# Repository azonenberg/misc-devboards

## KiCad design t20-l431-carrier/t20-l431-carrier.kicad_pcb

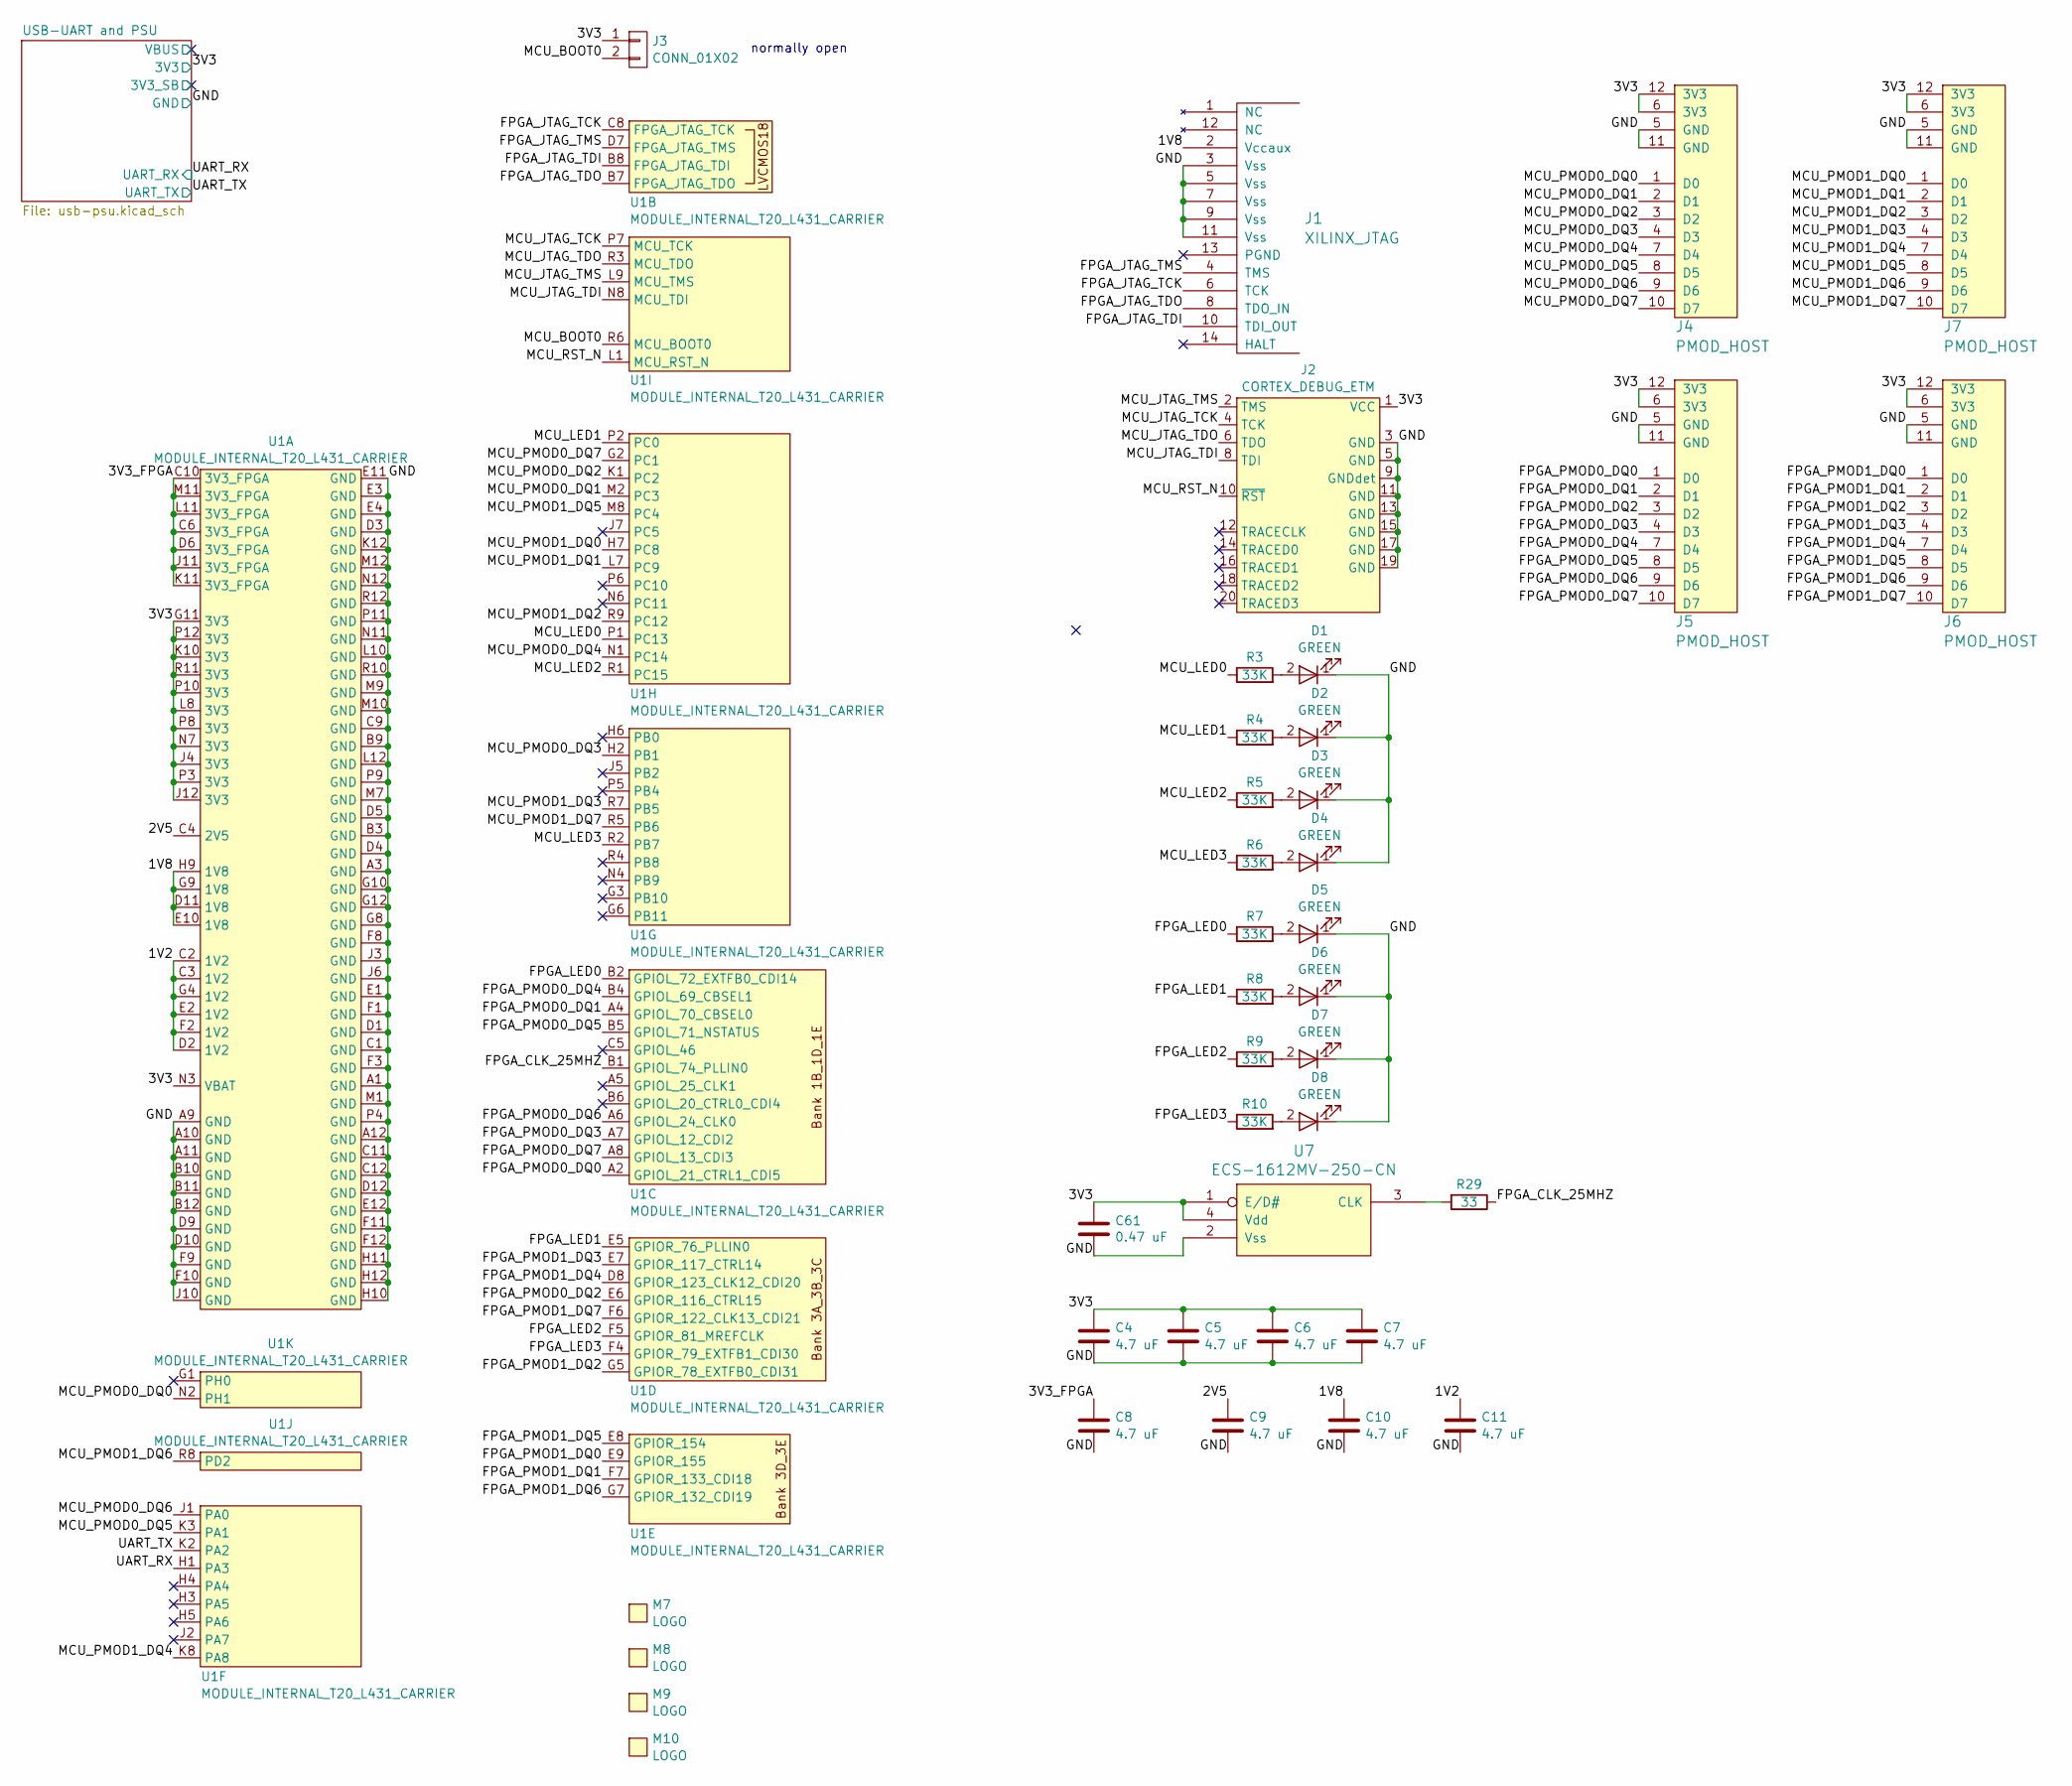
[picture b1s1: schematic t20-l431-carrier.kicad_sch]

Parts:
C4, C5, C6, C7, C8, C9, C10, C11: 4.7 uF; EIA_0603_CAP_NOSILK
C61: 0.47 uF; EIA_0402_CAP_NOSILK
D1, D2, D3, D4, D5, D6, D7, D8: GREEN; EIA_0402_LED
J1: XILINX_JTAG; XILINX_JTAG_PTH_MOLEX_0878311420
J2: CORTEX_DEBUG_ETM; CONN_HEADER_1.27MM_2x10_SMT_SAMTEC_FTSH-110-01-L-DV-K
J3: CONN_01X02; CONN_HEADER_2.54MM_1x2
J4, J5, J6, J7: PMOD_HOST; CONN_HEADER_2.54MM_2x6_RA_PMOD_HOST
M7: LOGO; LONGTHING-1200DPI
M8: LOGO; Logo_silk_ROHS_5x2.8mm
M9: LOGO; Logo_silk_WEEE_3.4x5mm
M10: LOGO; Logo_silk_OSHW_6x6mm
R3, R4, R5, R6, R7, R8, R9, R10: 33K; EIA_0402_RES_NOSILK
R29: 33; EIA_0402_RES_NOSILK
U1: MODULE_INTERNAL_T20_L431_CARRIER
U7: ECS-1612MV-250-CN; OSCILLATOR_1.6x1.2

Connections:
/1V2: C11.1, U1.C2 (1V2), U1.C3 (1V2), U1.D2 (1V2), U1.E2 (1V2), U1.F2 (1V2), U1.G4 (1V2)
/1V8: C10.1, J1.2 (Vccaux), U1.D11 (1V8), U1.E10 (1V8), U1.G9 (1V8), U1.H9 (1V8)
/2V5: C9.1, U1.C4 (2V5)
/3V3: C4.1, C5.1, C6.1, C7.1, C61.1, J2.1 (VCC), J3.1, J4.6 (3V3), J4.12 (3V3), J5.6 (3V3), J5.12 (3V3), J6.6 (3V3), J6.12 (3V3), J7.6 (3V3), J7.12 (3V3), U1.G11 (3V3), U1.J4 (3V3), U1.J12 (3V3), U1.K10 (3V3), U1.L8 (3V3), U1.N3 (VBAT), U1.N7 (3V3), U1.P3 (3V3), U1.P8 (3V3), U1.P10 (3V3), U1.P12 (3V3), U1.R11 (3V3), U7.1 (E/D#), U7.4 (Vdd); also elsewhere on the board
/3V3_FPGA: C8.1, U1.C6 (3V3_FPGA), U1.C10 (3V3_FPGA), U1.D6 (3V3_FPGA), U1.J11 (3V3_FPGA), U1.K11 (3V3_FPGA), U1.L11 (3V3_FPGA), U1.M11 (3V3_FPGA)
/FPGA_CLK_25MHZ: R29.1, U1.B1 (GPIOL_74_PLLIN0)
/FPGA_JTAG_TCK: J1.6 (TCK), U1.C8 (FPGA_JTAG_TCK)
/FPGA_JTAG_TDI: J1.10 (TDI_OUT), U1.B8 (FPGA_JTAG_TDI)
/FPGA_JTAG_TDO: J1.8 (TDO_IN), U1.B7 (FPGA_JTAG_TDO)
/FPGA_JTAG_TMS: J1.4 (TMS), U1.D7 (FPGA_JTAG_TMS)
/FPGA_LED0: R7.1, U1.B2 (GPIOL_72_EXTFB0_CDI14)
/FPGA_LED1: R8.1, U1.E5 (GPIOR_76_PLLIN0)
/FPGA_LED2: R9.1, U1.F5 (GPIOR_81_MREFCLK)
/FPGA_LED3: R10.1, U1.F4 (GPIOR_79_EXTFB1_CDI30)
/FPGA_PMOD0_DQ0: J5.1 (D0), U1.A2 (GPIOL_21_CTRL1_CDI5)
/FPGA_PMOD0_DQ1: J5.2 (D1), U1.A4 (GPIOL_70_CBSEL0)
/FPGA_PMOD0_DQ2: J5.3 (D2), U1.E6 (GPIOR_116_CTRL15)
/FPGA_PMOD0_DQ3: J5.4 (D3), U1.A7 (GPIOL_12_CDI2)
/FPGA_PMOD0_DQ4: J5.7 (D4), U1.B4 (GPIOL_69_CBSEL1)
/FPGA_PMOD0_DQ5: J5.8 (D5), U1.B5 (GPIOL_71_NSTATUS)
/FPGA_PMOD0_DQ6: J5.9 (D6), U1.A6 (GPIOL_24_CLK0)
/FPGA_PMOD0_DQ7: J5.10 (D7), U1.A8 (GPIOL_13_CDI3)
/FPGA_PMOD1_DQ0: J6.1 (D0), U1.E9 (GPIOR_155)
/FPGA_PMOD1_DQ1: J6.2 (D1), U1.F7 (GPIOR_133_CDI18)
/FPGA_PMOD1_DQ2: J6.3 (D2), U1.G5 (GPIOR_78_EXTFB0_CDI31)
/FPGA_PMOD1_DQ3: J6.4 (D3), U1.E7 (GPIOR_117_CTRL14)
/FPGA_PMOD1_DQ4: J6.7 (D4), U1.D8 (GPIOR_123_CLK12_CDI20)
/FPGA_PMOD1_DQ5: J6.8 (D5), U1.E8 (GPIOR_154)
/FPGA_PMOD1_DQ6: J6.9 (D6), U1.G7 (GPIOR_132_CDI19)
/FPGA_PMOD1_DQ7: J6.10 (D7), U1.F6 (GPIOR_122_CLK13_CDI21)
/GND: C4.2, C5.2, C6.2, C7.2, C8.2, C9.2, C10.2, C11.2, C61.2, D1.1 (K), D2.1 (K), D3.1 (K), D4.1 (K), D5.1 (K), D6.1 (K), D7.1 (K), D8.1 (K), J1.3 (Vss), J1.5 (Vss), J1.7 (Vss), J1.9 (Vss), J1.11 (Vss), J2.3 (GND), J2.5 (GND), J2.9 (GNDdet), J2.11 (GND), J2.13 (GND), J2.15 (GND), J2.17 (GND), J2.19 (GND), J4.5 (GND), J4.11 (GND), J5.5 (GND), J5.11 (GND), J6.5 (GND), J6.11 (GND), J7.5 (GND), J7.11 (GND), U1.A1 (GND), U1.A3 (GND), U1.A9 (GND), U1.A10 (GND), U1.A11 (GND), U1.A12 (GND), U1.B3 (GND), U1.B9 (GND), U1.B10 (GND), U1.B11 (GND), U1.B12 (GND), U1.C1 (GND), U1.C9 (GND), U1.C11 (GND), U1.C12 (GND), U1.D1 (GND), U1.D3 (GND), U1.D4 (GND), U1.D5 (GND), U1.D9 (GND), U1.D10 (GND), U1.D12 (GND), U1.E1 (GND), U1.E3 (GND), U1.E4 (GND), U1.E11 (GND), U1.E12 (GND), U1.F1 (GND), U1.F3 (GND), U1.F8 (GND), U1.F9 (GND), U1.F10 (GND), U1.F11 (GND), U1.F12 (GND), U1.G8 (GND), U1.G10 (GND), U1.G12 (GND), U1.H10 (GND), U1.H11 (GND), U1.H12 (GND), U1.J3 (GND), U1.J6 (GND), U1.J10 (GND), U1.K12 (GND), U1.L10 (GND), U1.L12 (GND), U1.M1 (GND), U1.M7 (GND), U1.M9 (GND), U1.M10 (GND), U1.M12 (GND), U1.N11 (GND), U1.N12 (GND), U1.P4 (GND), U1.P9 (GND), U1.P11 (GND), U1.R10 (GND), U1.R12 (GND), U7.2 (Vss); also elsewhere on the board
/MCU_BOOT0: J3.2, U1.R6 (MCU_BOOT0)
/MCU_JTAG_TCK: J2.4 (TCK), U1.P7 (MCU_TCK)
/MCU_JTAG_TDI: J2.8 (TDI), U1.N8 (MCU_TDI)
/MCU_JTAG_TDO: J2.6 (TDO), U1.R3 (MCU_TDO)
/MCU_JTAG_TMS: J2.2 (TMS), U1.L9 (MCU_TMS)
/MCU_LED0: R3.1, U1.P1 (PC13)
/MCU_LED1: R4.1, U1.P2 (PC0)
/MCU_LED2: R5.1, U1.R1 (PC15)
/MCU_LED3: R6.1, U1.R2 (PB7)
/MCU_PMOD0_DQ0: J4.1 (D0), U1.N2 (PH1)
/MCU_PMOD0_DQ1: J4.2 (D1), U1.M2 (PC3)
/MCU_PMOD0_DQ2: J4.3 (D2), U1.K1 (PC2)
/MCU_PMOD0_DQ3: J4.4 (D3), U1.H2 (PB1)
/MCU_PMOD0_DQ4: J4.7 (D4), U1.N1 (PC14)
/MCU_PMOD0_DQ5: J4.8 (D5), U1.K3 (PA1)
/MCU_PMOD0_DQ6: J4.9 (D6), U1.J1 (PA0)
/MCU_PMOD0_DQ7: J4.10 (D7), U1.G2 (PC1)
/MCU_PMOD1_DQ0: J7.1 (D0), U1.H7 (PC8)
/MCU_PMOD1_DQ1: J7.2 (D1), U1.L7 (PC9)
/MCU_PMOD1_DQ2: J7.3 (D2), U1.R9 (PC12)
/MCU_PMOD1_DQ3: J7.4 (D3), U1.R7 (PB5)
/MCU_PMOD1_DQ4: J7.7 (D4), U1.K8 (PA8)
/MCU_PMOD1_DQ5: J7.8 (D5), U1.M8 (PC4)
/MCU_PMOD1_DQ6: J7.9 (D6), U1.R8 (PD2)
/MCU_PMOD1_DQ7: J7.10 (D7), U1.R5 (PB6)
/MCU_RST_N: J2.10 (~RST), U1.L1 (MCU_RST_N)
/UART_RX: U1.H1 (PA3); also elsewhere on the board
/UART_TX: U1.K2 (PA2); also elsewhere on the board
unnamed: D1.2 (A), R3.2
unnamed: D2.2 (A), R4.2
unnamed: D3.2 (A), R5.2
unnamed: D4.2 (A), R6.2
unnamed: D5.2 (A), R7.2
unnamed: D6.2 (A), R8.2
unnamed: D7.2 (A), R9.2
unnamed: D8.2 (A), R10.2
unnamed: R29.2, U7.3 (CLK)

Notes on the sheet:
normally open

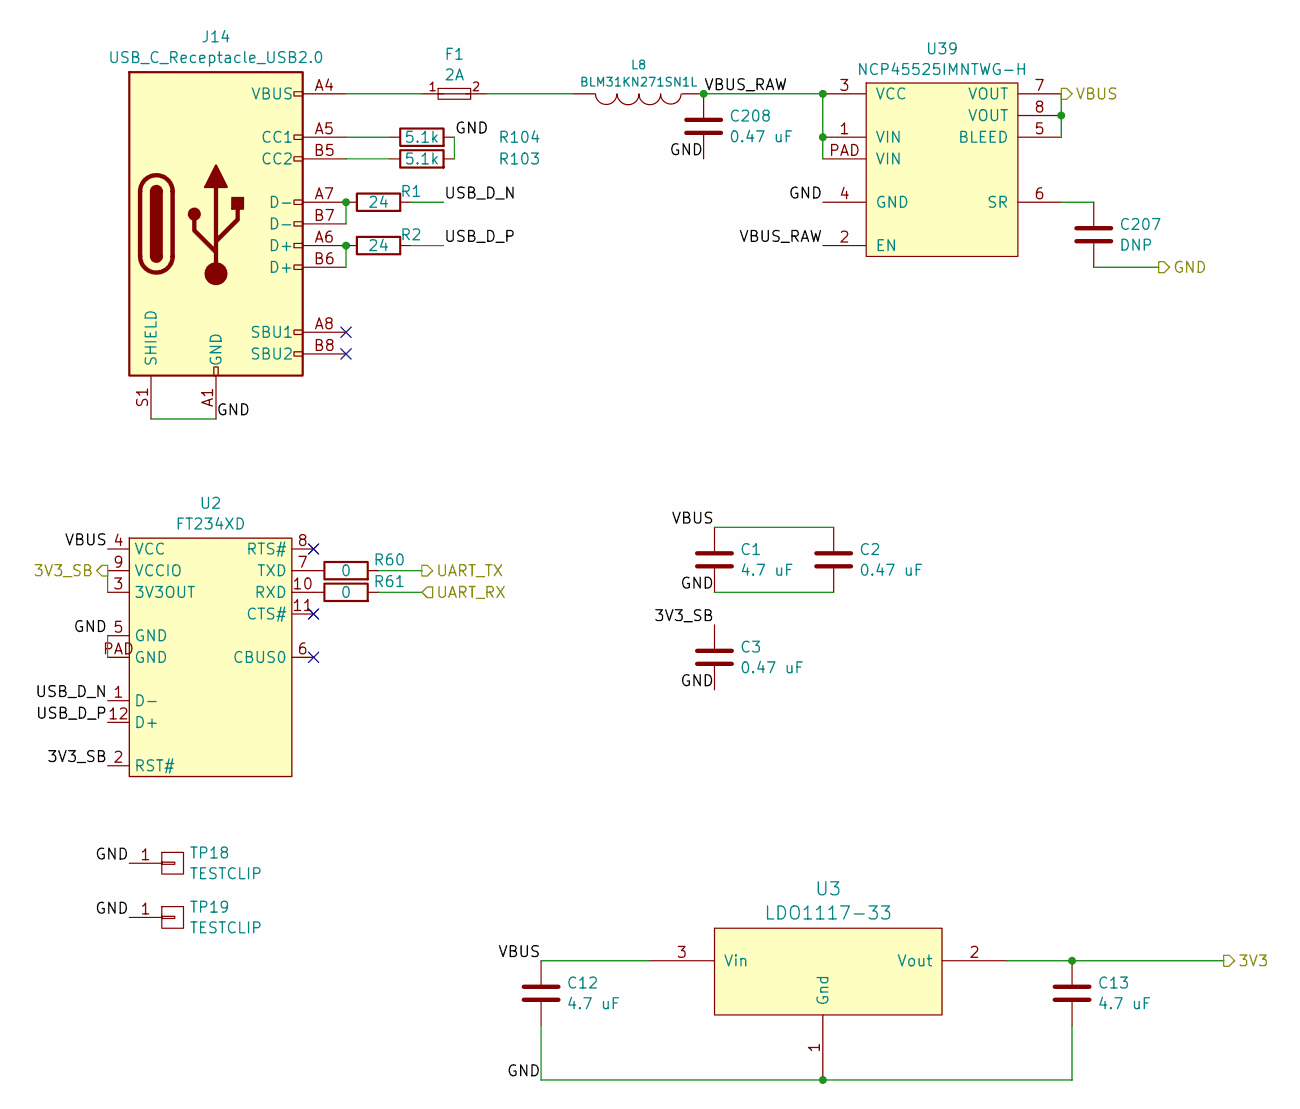
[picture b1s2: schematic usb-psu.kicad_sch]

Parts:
C1, C12, C13: 4.7 uF; EIA_0603_CAP_NOSILK
C2, C3, C208: 0.47 uF; EIA_0402_CAP_NOSILK
C207: DNP; EIA_0402_CAP_NOSILK
F1: 2A; EIA_0402_RES_NOSILK
J14: USB_C_Receptacle_USB2.0; GCT_USB4500-03-0-A-PIP
L8: BLM31KN271SN1L; EIA_1206_CAP_NOSILK
R1, R2: 24; EIA_0402_RES_NOSILK
R60, R61: 0; EIA_0402_RES_NOSILK
R103, R104: 5.1k; EIA_0402_RES_NOSILK
TP18, TP19: TESTCLIP; TESTPOINT_SMT_KEYSTONE_5016
U2: FT234XD; DFN_12_0.45MM_3x3MM
U3: LDO1117-33; SOT223-4
U39: NCP45525IMNTWG-H; DFN_8_0.5MM_2x2MM

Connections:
/3V3: C13.1, U3.2 (Vout); also elsewhere on the board
/GND: C1.2, C2.2, C3.2, C12.2, C13.2, C207.2, C208.2, J14.A1 (GND), J14.A12 (GND), J14.B1 (GND), J14.B12 (GND), J14.S1 (SHIELD), R103.2, R104.2, TP18.1, TP19.1, U2.5 (GND), U2.PAD (GND), U3.1 (Gnd), U39.4 (GND); also elsewhere on the board
/UART_RX: R61.2; also elsewhere on the board
/UART_TX: R60.2; also elsewhere on the board
/USB-UART and PSU/3V3_SB: C3.1, U2.2 (RST#), U2.3 (3V3OUT), U2.9 (VCCIO)
/USB-UART and PSU/USB_D_N: R1.2, U2.1 (D-)
/USB-UART and PSU/USB_D_P: R2.2, U2.12 (D+)
/USB-UART and PSU/VBUS: C1.1, C2.1, C12.1, U2.4 (VCC), U3.3 (Vin), U39.5 (BLEED), U39.7 (VOUT), U39.8 (VOUT)
/USB-UART and PSU/VBUS_RAW: C208.1, L8.1, U39.1 (VIN), U39.2 (EN), U39.3 (VCC), U39.PAD (VIN)
unnamed: F1.1, J14.A4 (VBUS), J14.A9 (VBUS), J14.B4 (VBUS), J14.B9 (VBUS)
unnamed: F1.2, L8.2
unnamed: J14.A5 (CC1), R104.1
unnamed: J14.B5 (CC2), R103.1
unnamed: J14.A6 (D+), J14.B6 (D+), R2.1
unnamed: J14.A7 (D-), J14.B7 (D-), R1.1
unnamed: R61.1, U2.10 (RXD)
unnamed: R60.1, U2.7 (TXD)
unnamed: C207.1, U39.6 (SR)

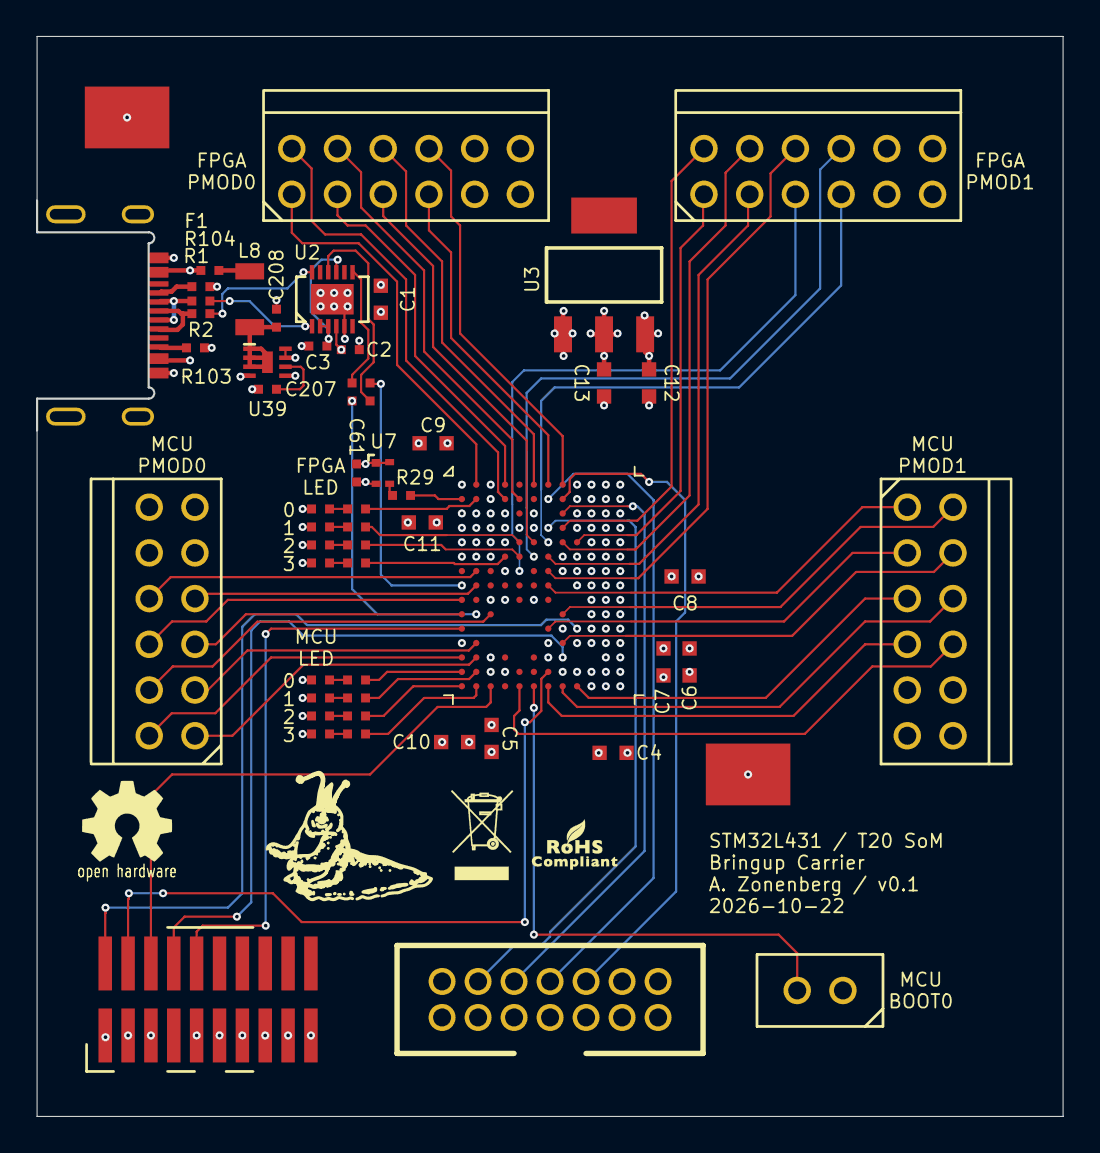
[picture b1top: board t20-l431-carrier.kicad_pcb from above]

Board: 4 copper layers, 57.0 x 60.0 mm, 60 parts (0 on the bottom side), 82 nets.

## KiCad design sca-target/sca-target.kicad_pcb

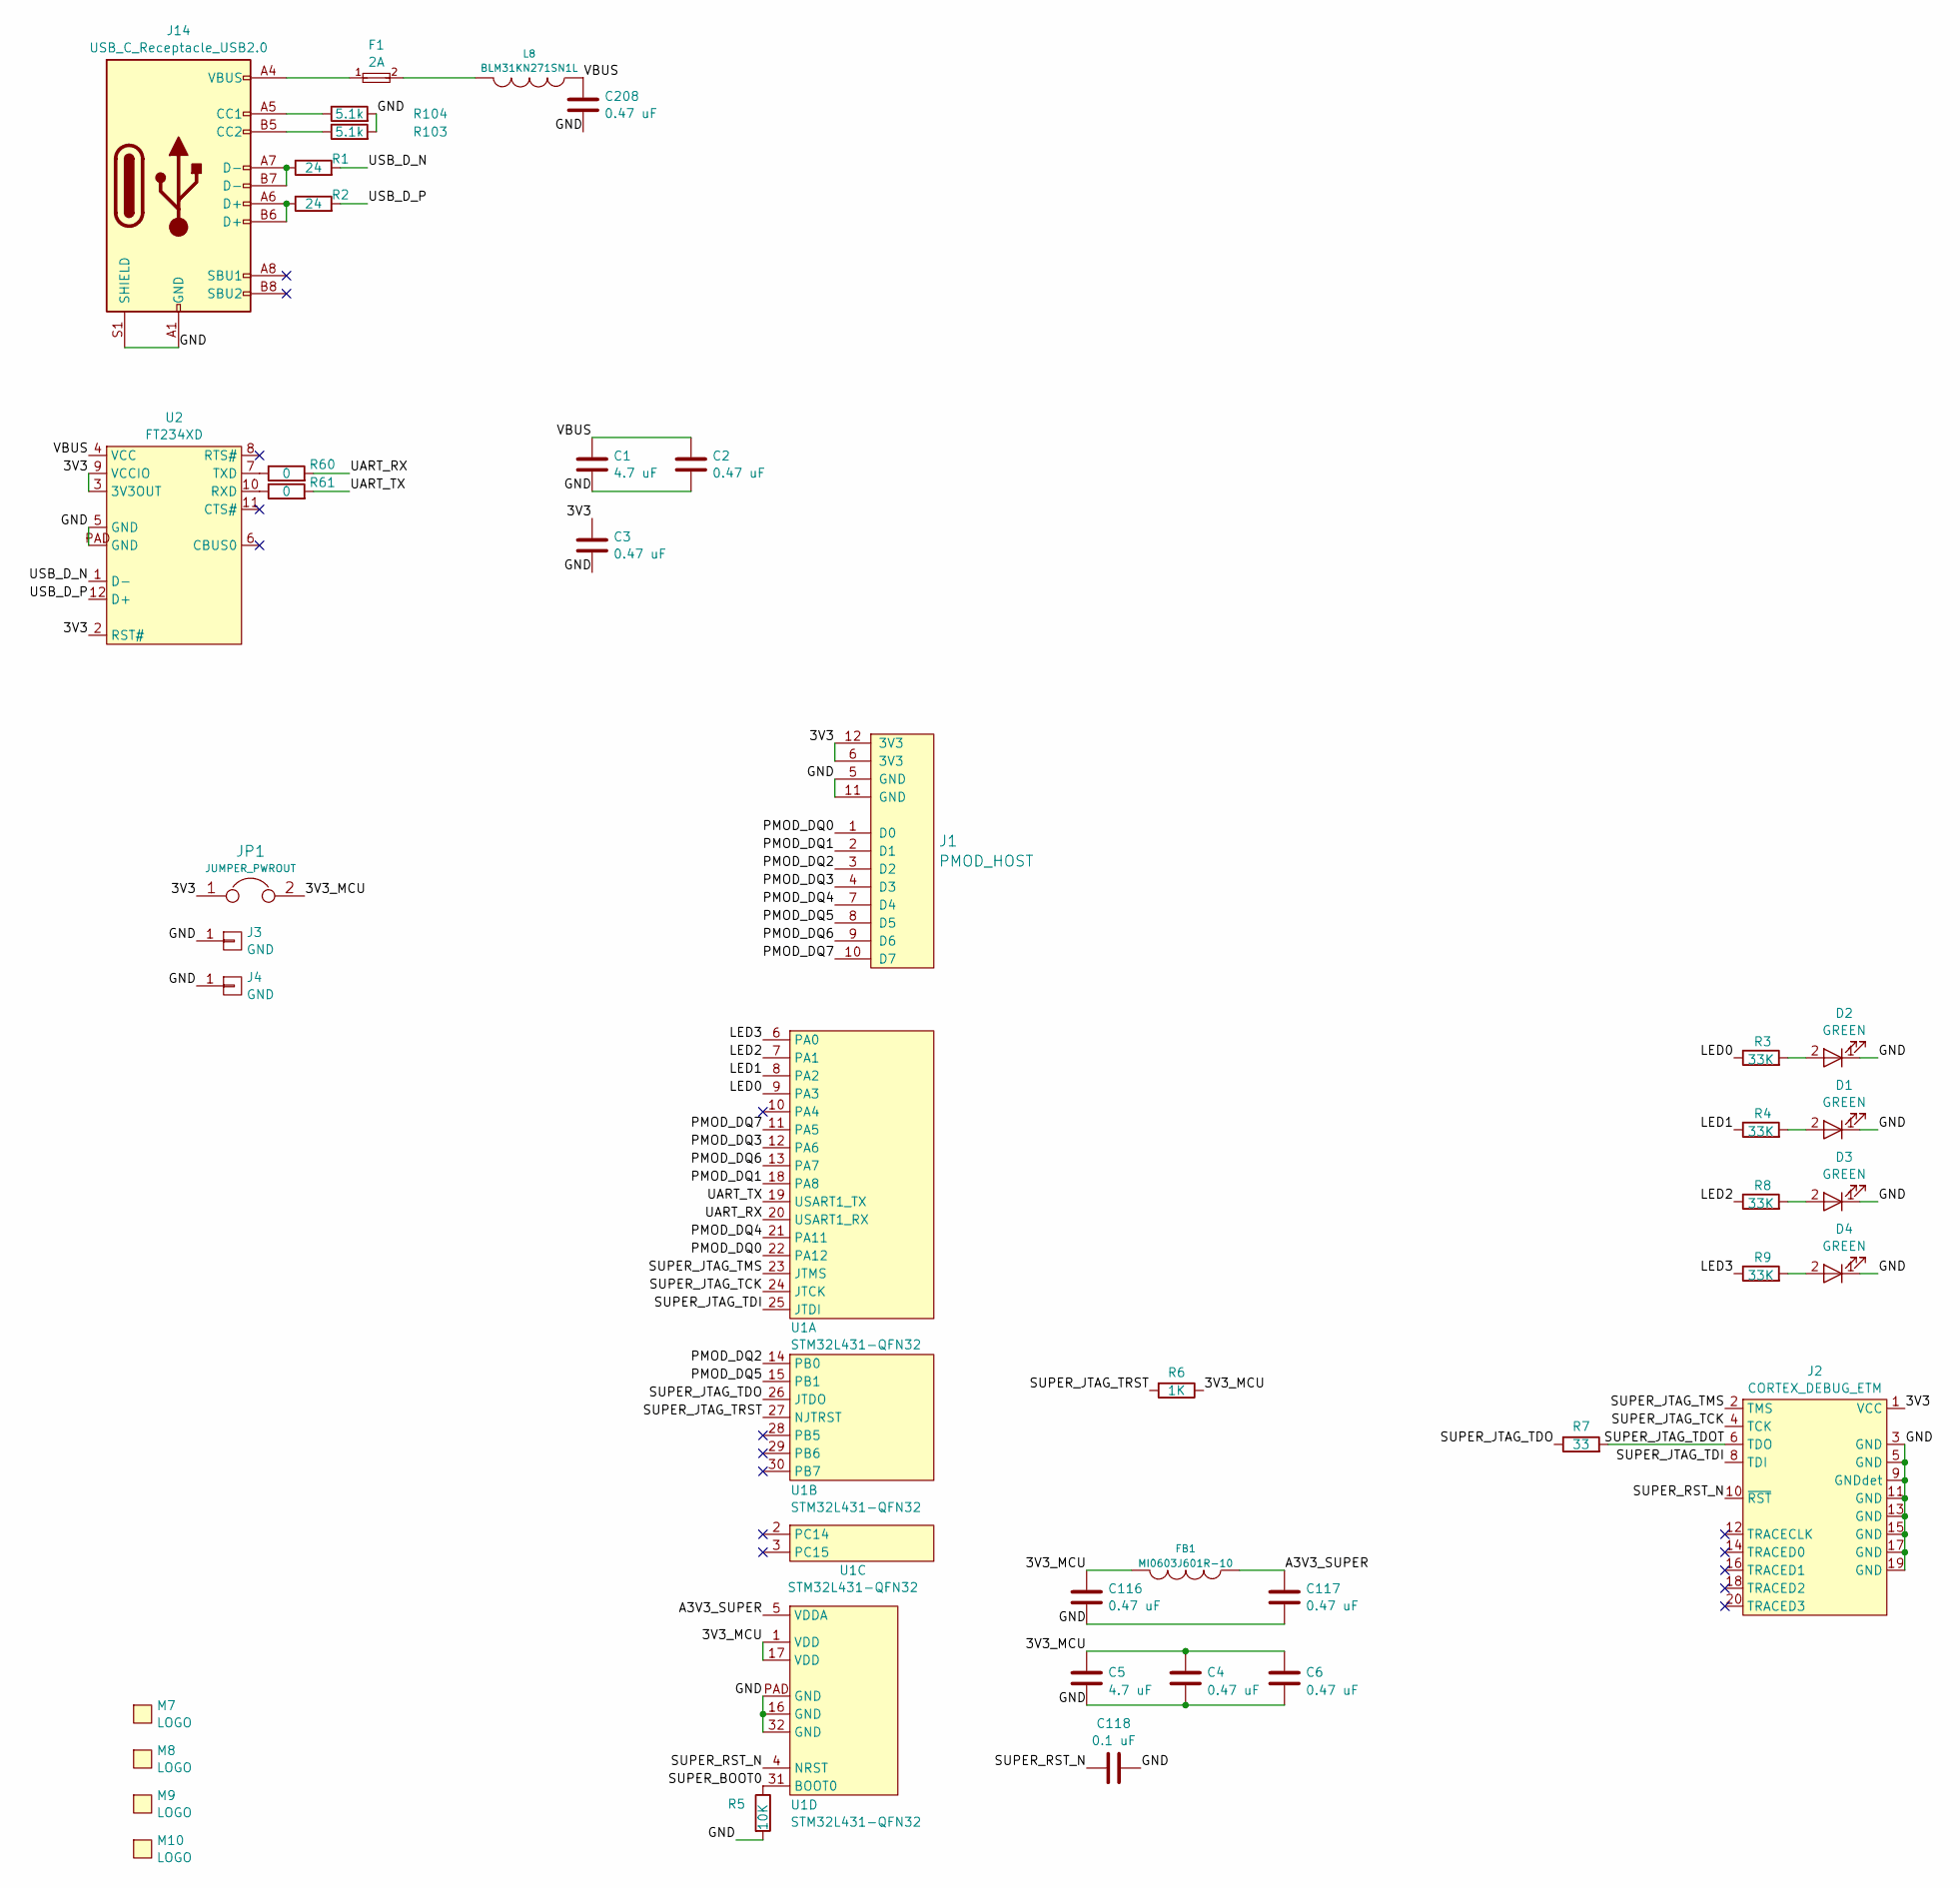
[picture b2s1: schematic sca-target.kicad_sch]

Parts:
C1, C5: 4.7 uF; EIA_0603_CAP_NOSILK
C2, C3, C4, C6, C116, C117, C208: 0.47 uF; EIA_0402_CAP_NOSILK
C118: 0.1 uF; EIA_0402_CAP_NOSILK
D1, D2, D3, D4: GREEN; EIA_0402_LED
F1: 2A; EIA_0402_RES_NOSILK
FB1: MI0603J601R-10; EIA_0603_INDUCTOR_NOSILK
J1: PMOD_HOST; CONN_HEADER_2.54MM_2x6_RA_PMOD_HOST
J2: CORTEX_DEBUG_ETM; CONN_HEADER_1.27MM_2x10_SMT_SAMTEC_FTSH-110-01-L-DV-K
J3, J4: GND; CONN_HEADER_2.54MM_1x1
J14: USB_C_Receptacle_USB2.0; GCT_USB4500-03-0-A-PIP
JP1: JUMPER_PWROUT; CONN_HEADER_2.54MM_1x2
L8: BLM31KN271SN1L; EIA_1206_CAP_NOSILK
M7: LOGO; LONGTHING-1200DPI
M8: LOGO; Logo_silk_ROHS_5x2.8mm
M9: LOGO; Logo_silk_WEEE_3.4x5mm
M10: LOGO; Logo_silk_OSHW_6x6mm
R1, R2: 24; EIA_0402_RES_NOSILK
R3, R4, R8, R9: 33K; EIA_0402_RES_NOSILK
R5: 10K; EIA_0402_RES_NOSILK
R6: 1K; EIA_0402_RES_NOSILK
R7: 33; EIA_0402_RES_NOSILK
R60, R61: 0; EIA_0402_RES_NOSILK
R103, R104: 5.1k; EIA_0402_RES_NOSILK
U1: STM32L431-QFN32; QFN_32_0.5MM_5x5MM
U2: FT234XD; DFN_12_0.45MM_3x3MM

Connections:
/3V3: C3.1, J1.6 (3V3), J1.12 (3V3), J2.1 (VCC), JP1.1, U2.2 (RST#), U2.3 (3V3OUT), U2.9 (VCCIO)
/3V3_MCU: C4.1, C5.1, C6.1, C116.1, FB1.2, JP1.2, R6.1, U1.1 (VDD), U1.17 (VDD)
/A3V3_SUPER: C117.1, FB1.1, U1.5 (VDDA)
/GND: C1.2, C2.2, C3.2, C4.2, C5.2, C6.2, C116.2, C117.2, C118.2, C208.2, D1.1 (K), D2.1 (K), D3.1 (K), D4.1 (K), J1.5 (GND), J1.11 (GND), J2.3 (GND), J2.5 (GND), J2.9 (GNDdet), J2.11 (GND), J2.13 (GND), J2.15 (GND), J2.17 (GND), J2.19 (GND), J3.1, J4.1, J14.A1 (GND), J14.A12 (GND), J14.B1 (GND), J14.B12 (GND), J14.S1 (SHIELD), R5.2, R103.2, R104.2, U1.16 (GND), U1.32 (GND), U1.PAD (GND), U2.5 (GND), U2.PAD (GND)
/LED0: R3.1, U1.9 (PA3)
/LED1: R4.1, U1.8 (PA2)
/LED2: R8.1, U1.7 (PA1)
/LED3: R9.1, U1.6 (PA0)
/PMOD_DQ0: J1.1 (D0), U1.22 (PA12)
/PMOD_DQ1: J1.2 (D1), U1.18 (PA8)
/PMOD_DQ2: J1.3 (D2), U1.14 (PB0)
/PMOD_DQ3: J1.4 (D3), U1.12 (PA6)
/PMOD_DQ4: J1.7 (D4), U1.21 (PA11)
/PMOD_DQ5: J1.8 (D5), U1.15 (PB1)
/PMOD_DQ6: J1.9 (D6), U1.13 (PA7)
/PMOD_DQ7: J1.10 (D7), U1.11 (PA5)
/SUPER_BOOT0: R5.1, U1.31 (BOOT0)
/SUPER_JTAG_TCK: J2.4 (TCK), U1.24 (JTCK)
/SUPER_JTAG_TDI: J2.8 (TDI), U1.25 (JTDI)
/SUPER_JTAG_TDO: R7.1, U1.26 (JTDO)
/SUPER_JTAG_TDOT: J2.6 (TDO), R7.2
/SUPER_JTAG_TMS: J2.2 (TMS), U1.23 (JTMS)
/SUPER_JTAG_TRST: R6.2, U1.27 (NJTRST)
/SUPER_RST_N: C118.1, J2.10 (~RST), U1.4 (NRST)
/UART_RX: R60.2, U1.20 (USART1_RX)
/UART_TX: R61.2, U1.19 (USART1_TX)
/USB_D_N: R1.2, U2.1 (D-)
/USB_D_P: R2.2, U2.12 (D+)
/VBUS: C1.1, C2.1, C208.1, L8.1, U2.4 (VCC)
unnamed: D1.2 (A), R4.2
unnamed: D2.2 (A), R3.2
unnamed: D3.2 (A), R8.2
unnamed: D4.2 (A), R9.2
unnamed: F1.1, J14.A4 (VBUS), J14.A9 (VBUS), J14.B4 (VBUS), J14.B9 (VBUS)
unnamed: F1.2, L8.2
unnamed: J14.A5 (CC1), R104.1
unnamed: J14.B5 (CC2), R103.1
unnamed: J14.A6 (D+), J14.B6 (D+), R2.1
unnamed: J14.A7 (D-), J14.B7 (D-), R1.1
unnamed: R61.1, U2.10 (RXD)
unnamed: R60.1, U2.7 (TXD)

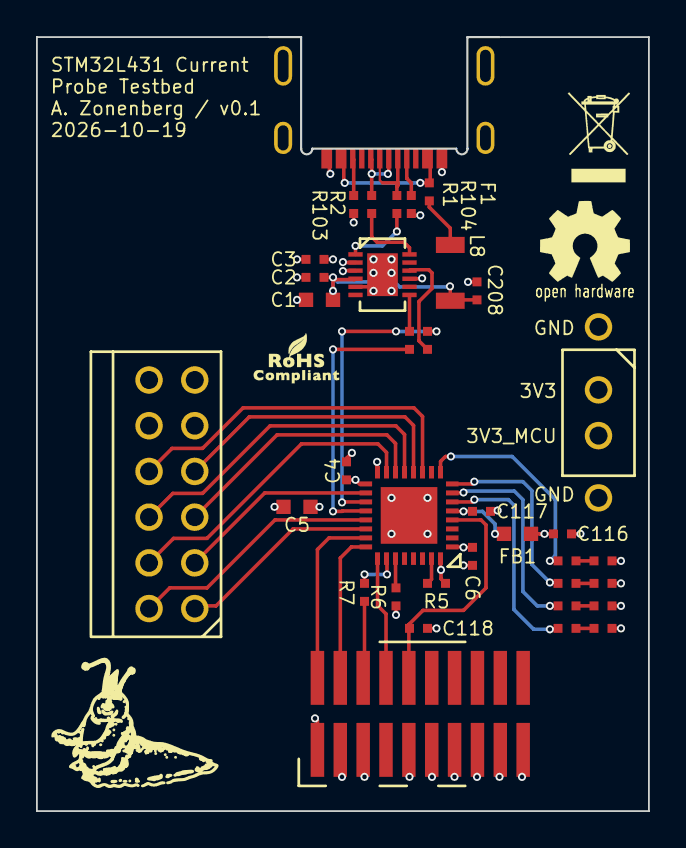
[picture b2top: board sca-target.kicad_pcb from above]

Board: 4 copper layers, 34.0 x 43.0 mm, 42 parts (0 on the bottom side), 41 nets.

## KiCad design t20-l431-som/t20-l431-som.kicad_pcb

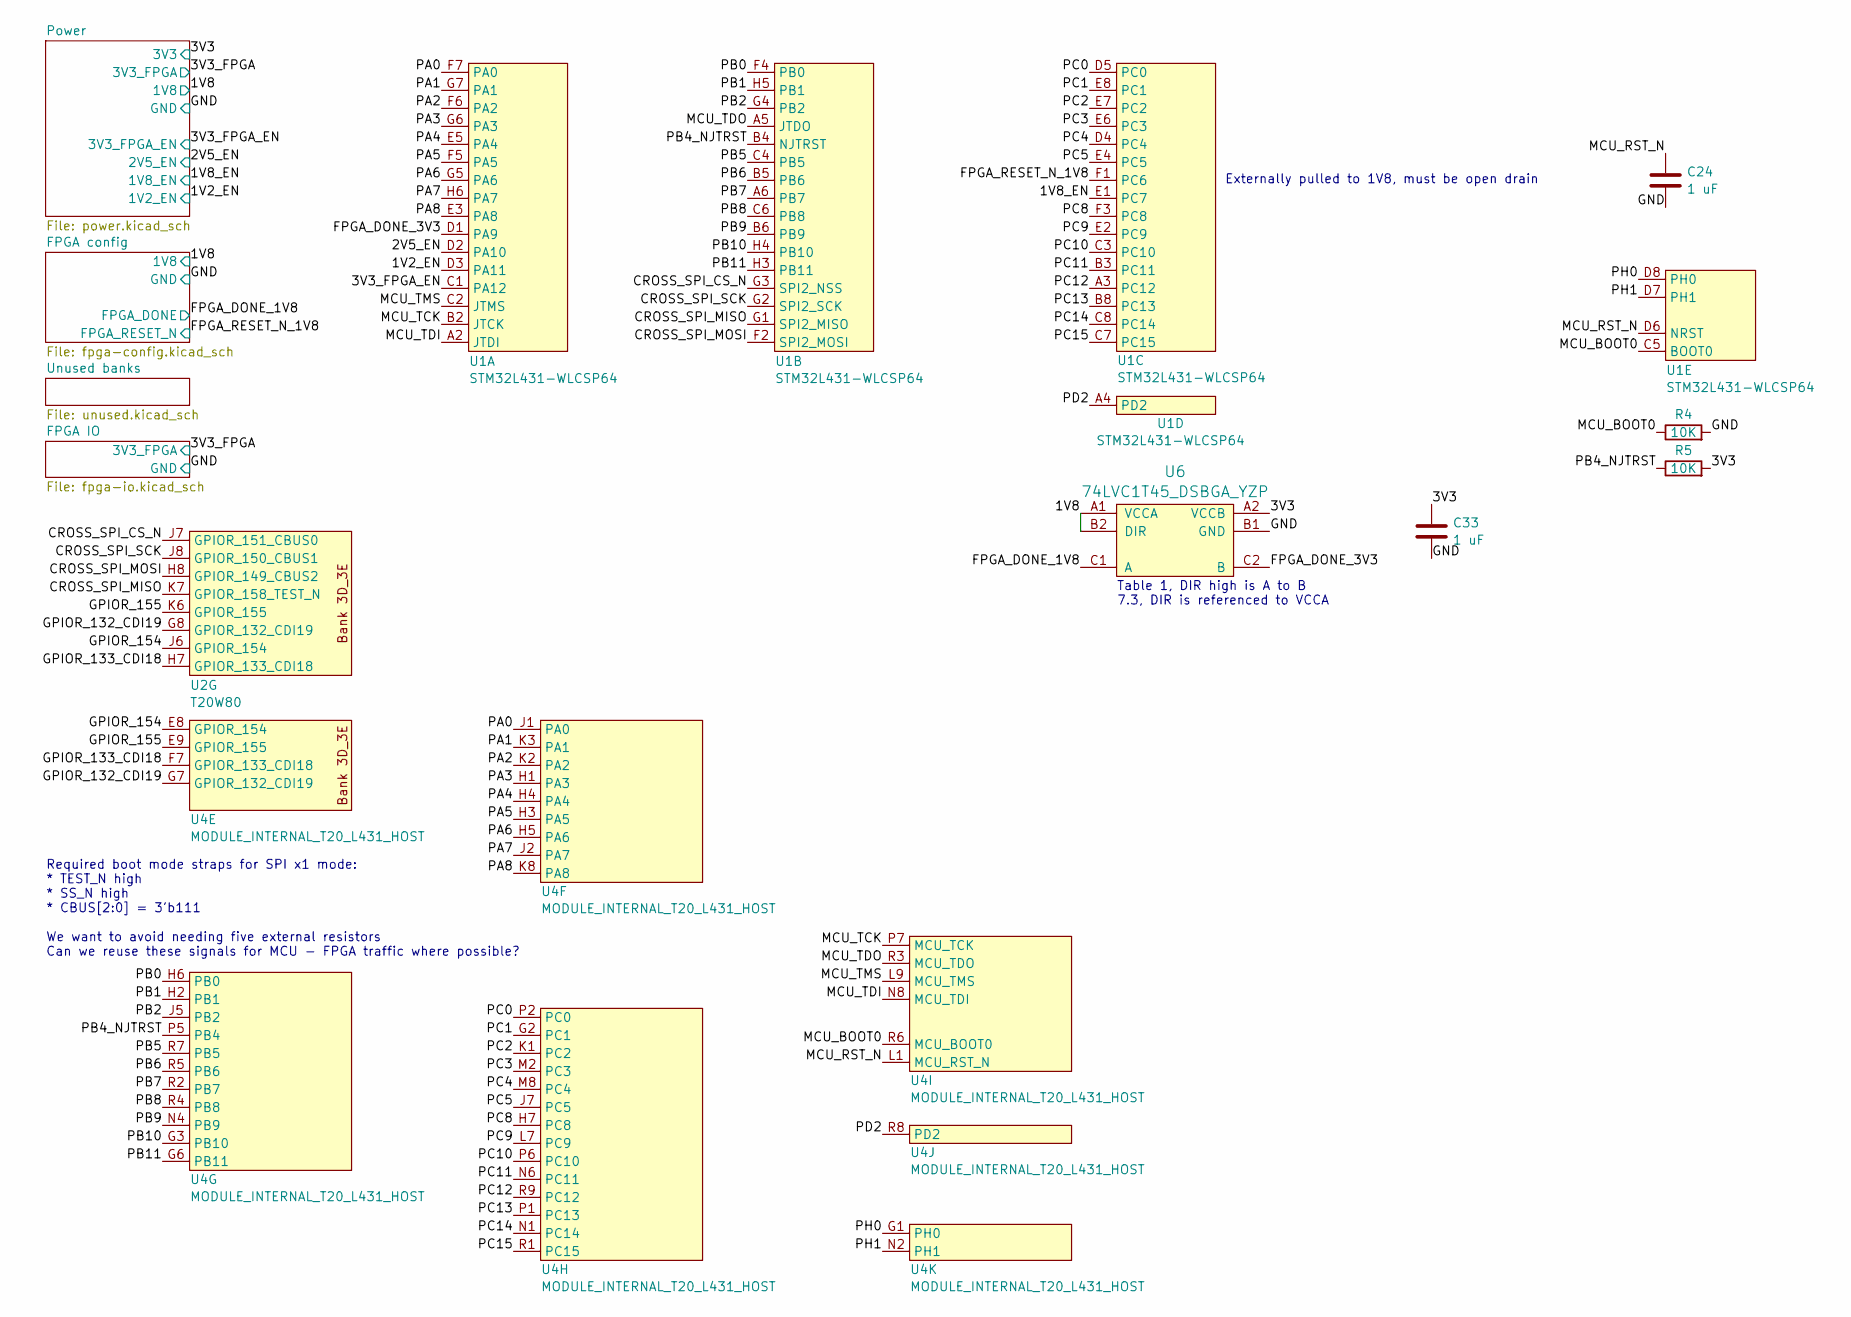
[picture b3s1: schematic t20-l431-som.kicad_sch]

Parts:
C24, C33: 1 uF; EIA_0201_CAP_NOSILK; MPN GRM033C80J105ME05D
R4, R5: 10K; EIA_0201_RES_NOSILK
U1: STM32L431-WLCSP64; BGA_64_0.35MM_3p1MM_STM32L431
U2: T20W80; BGA_80_0.4MM_4p4x3p5_T20W80
U4: MODULE_INTERNAL_T20_L431_HOST
U6: 74LVC1T45_DSBGA_YZP; BGA_6_1.5x0.9_0.5MM_TI_YZP

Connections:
/1V2_EN: U1.D3 (PA11); also elsewhere on the board
/1V8: U6.A1 (VCCA), U6.B2 (DIR); also elsewhere on the board
/1V8_EN: U1.E1 (PC7); also elsewhere on the board
/2V5_EN: U1.D2 (PA10); also elsewhere on the board
/3V3: C33.1, R5.2, U6.A2 (VCCB); also elsewhere on the board
/3V3_FPGA_EN: U1.C1 (PA12); also elsewhere on the board
/CROSS_SPI_CS_N: U1.G3 (SPI2_NSS), U2.J7 (GPIOR_151_CBUS0)
/CROSS_SPI_MISO: U1.G1 (SPI2_MISO), U2.K7 (GPIOR_158_TEST_N)
/CROSS_SPI_MOSI: U1.F2 (SPI2_MOSI), U2.H8 (GPIOR_149_CBUS2)
/CROSS_SPI_SCK: U1.G2 (SPI2_SCK), U2.J8 (GPIOR_150_CBUS1)
/FPGA_DONE_1V8: U6.C1 (A); also elsewhere on the board
/FPGA_DONE_3V3: U1.D1 (PA9), U6.C2 (B)
/FPGA_RESET_N_1V8: U1.F1 (PC6); also elsewhere on the board
/GND: C24.2, C33.2, R4.2, U6.B1 (GND); also elsewhere on the board
/GPIOR_132_CDI19: U2.G8 (GPIOR_132_CDI19), U4.G7 (GPIOR_132_CDI19)
/GPIOR_133_CDI18: U2.H7 (GPIOR_133_CDI18), U4.F7 (GPIOR_133_CDI18)
/GPIOR_154: U2.J6 (GPIOR_154), U4.E8 (GPIOR_154)
/GPIOR_155: U2.K6 (GPIOR_155), U4.E9 (GPIOR_155)
/MCU_BOOT0: R4.1, U1.C5 (BOOT0), U4.R6 (MCU_BOOT0)
/MCU_RST_N: C24.1, U1.D6 (NRST), U4.L1 (MCU_RST_N)
/MCU_TCK: U1.B2 (JTCK), U4.P7 (MCU_TCK)
/MCU_TDI: U1.A2 (JTDI), U4.N8 (MCU_TDI)
/MCU_TDO: U1.A5 (JTDO), U4.R3 (MCU_TDO)
/MCU_TMS: U1.C2 (JTMS), U4.L9 (MCU_TMS)
/PA0: U1.F7 (PA0), U4.J1 (PA0)
/PA1: U1.G7 (PA1), U4.K3 (PA1)
/PA2: U1.F6 (PA2), U4.K2 (PA2)
/PA3: U1.G6 (PA3), U4.H1 (PA3)
/PA4: U1.E5 (PA4), U4.H4 (PA4)
/PA5: U1.F5 (PA5), U4.H3 (PA5)
/PA6: U1.G5 (PA6), U4.H5 (PA6)
/PA7: U1.H6 (PA7), U4.J2 (PA7)
/PA8: U1.E3 (PA8), U4.K8 (PA8)
/PB0: U1.F4 (PB0), U4.H6 (PB0)
/PB1: U1.H5 (PB1), U4.H2 (PB1)
/PB2: U1.G4 (PB2), U4.J5 (PB2)
/PB4_NJTRST: R5.1, U1.B4 (NJTRST), U4.P5 (PB4)
/PB5: U1.C4 (PB5), U4.R7 (PB5)
/PB6: U1.B5 (PB6), U4.R5 (PB6)
/PB7: U1.A6 (PB7), U4.R2 (PB7)
/PB8: U1.C6 (PB8), U4.R4 (PB8)
/PB9: U1.B6 (PB9), U4.N4 (PB9)
/PB10: U1.H4 (PB10), U4.G3 (PB10)
/PB11: U1.H3 (PB11), U4.G6 (PB11)
/PC0: U1.D5 (PC0), U4.P2 (PC0)
/PC1: U1.E8 (PC1), U4.G2 (PC1)
/PC2: U1.E7 (PC2), U4.K1 (PC2)
/PC3: U1.E6 (PC3), U4.M2 (PC3)
/PC4: U1.D4 (PC4), U4.M8 (PC4)
/PC5: U1.E4 (PC5), U4.J7 (PC5)
/PC8: U1.F3 (PC8), U4.H7 (PC8)
/PC9: U1.E2 (PC9), U4.L7 (PC9)
/PC10: U1.C3 (PC10), U4.P6 (PC10)
/PC11: U1.B3 (PC11), U4.N6 (PC11)
/PC12: U1.A3 (PC12), U4.R9 (PC12)
/PC13: U1.B8 (PC13), U4.P1 (PC13)
/PC14: U1.C8 (PC14), U4.N1 (PC14)
/PC15: U1.C7 (PC15), U4.R1 (PC15)
/PD2: U1.A4 (PD2), U4.R8 (PD2)
/PH0: U1.D8 (PH0), U4.G1 (PH0)
/PH1: U1.D7 (PH1), U4.N2 (PH1)

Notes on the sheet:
Table 1, DIR high is A to B 7.3, DIR is referenced to VCCA
Required boot mode straps for SPI x1 mode: * TEST_N high * SS_N high * CBUS[2:0] = 3'b111 We want to avoid needing five external resistors Can we reuse these signals for MCU - FPGA traffic where possible?
Externally pulled to 1V8, must be open drain

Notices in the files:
baset1-media-converter/firmware/main.cpp:
Copyright (c) 2024 Andrew D. Zonenberg and contributors
All rights reserved.
